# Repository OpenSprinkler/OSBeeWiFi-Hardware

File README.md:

## OpenSprinkler Bee WiFi Eagle Files

This folder contains EagleCAD schematic and board design files for OpenSprinkler Bee WiFi circuit. Please use EagleCAD 7.0 or above to view the files. We generally do not provide BOM, but you can use EagleCAD's BOM script to export a BOM yourself.

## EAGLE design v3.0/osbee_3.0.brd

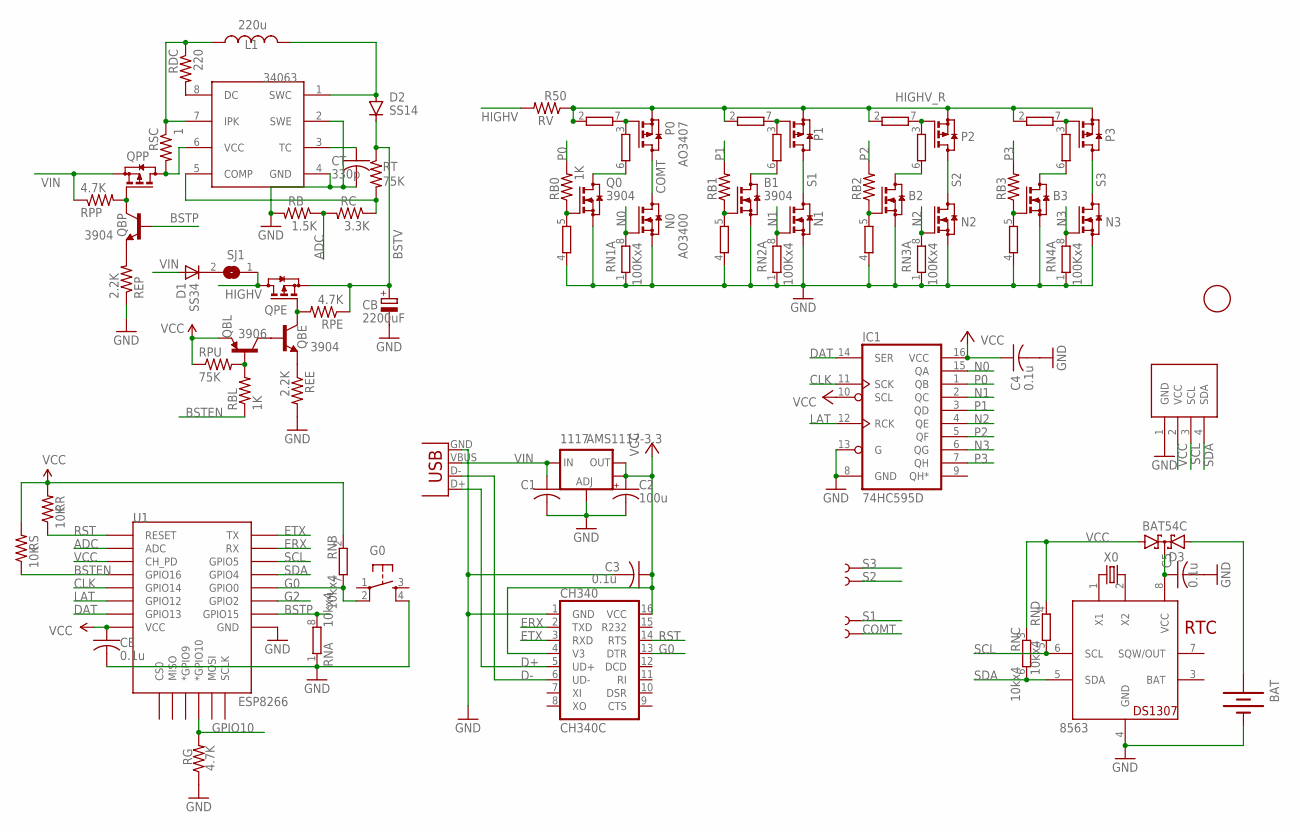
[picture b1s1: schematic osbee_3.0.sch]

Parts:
1F: FIDUCIAL; FIDUCIAL_1MM
1117: AMS1117-3.3; SOT223
8563: PCF8563; SO08
34063: MC34063; SO08
B1, B2, B3: 3904; SOT23
BAT: BATTERYBATTERY_12MM_SMT; BATTCON_12MM_SMT
C1: 10u; C0805K
C2: 100u; PANASONIC_C
C3: 0.1u; C0603K
C4, C5: 0.1u; C0603
CB: 2200uF; E5-8,5
CE: 0.1u; C0603
CH340: CH340C; SO16
CT: 330p; C0603K
D1: SS34; SMB-DIODE
D2: SS14; DO-214AC
D3: BAT54C; SOT23
G0: SPST_TACT; EVQ-Q2-SMD
IC1: 74HC595D; SO16
L1: 220u; CR54
N0, N1, N2, N3: AO3400; SOT23
P0, P1, P2, P3: AO3407; SOT23
Q0: 3904; SOT23
QBE: 3904; SOT23-3
QBL: 3906; SOT23-3
QBP: 3904; SOT23-3
QPE: AO3407; SOT23
QPP: AO3407; SOT23
RB: 1.5K; R0603
RB0, RB1, RB2, RB3: 1K; R0603
RBL: 1K; R0603
RC: 3.3K; R0603
RDC: 220; R0603
REE: 2.2K; R0603
REP: 2.2K; R0603
RG: 4.7K; R0603
RN: 10kx4; EXB38V
RN1, RN2, RN3, RN4: 100Kx4; EXB38V
RPE: 4.7K; R0603
RPP: 4.7K; R0603
RPU: 75K; R0603
RR: 10K; R0603
RS: 10K; R0603
RSC: 1; R0603
RT: 75K; R0603
RV: R50; R2512
SJ1: SJ
ST1, ST2, ST3: NOBOM-; PETAL-9X9
STT: NOBOM-; PETAL-9X9
U1: ESP8266; ESP12E-SMD
U$1: NOBOM-OLED; SSD1306_OLED_I2C_PCB_0.75_BNEW
USB: USBMICROB2; USB-MICROB2
X0: 32.768kHz; 3.2X1.5

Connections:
ADC: RB.1, RC.2, U1.ADC
BAT: 8563.3 (BAT)
BSTEN: RBL.1, RS.1, U1.GPIO16
BSTP: QBP.1 (B), RN.8 (2), U1.GPIO15
BSTV: CB.+, D2.C, QPE.2 (S), RPE.1, RT.1
CLK: IC1.11 (SCK), U1.GPIO14
COMT: N0.3 (D), P0.3 (D), STT.P$1
D+: CH340.5 (UD+), USB.D+
D-: CH340.6 (UD-), USB.D-
DAT: IC1.14 (SER), U1.GPIO13
ERX: CH340.2 (TXD), U1.RXD0 (RX)
ETX: CH340.3 (RXD), U1.TXD0 (TX)
G0: CH340.13 (DTR), G0.2, RN.7 (2), U1.GPIO0
G2: U1.GPIO2
GND: 1117.1 (ADJ), 8563.4 (GND), 34063.2 (SWE), 34063.4 (GND), B1.2 (S), B2.2 (S), B3.2 (S), BAT.P$1 (-), C1.2, C2.-, C3.2, C4.2, C5.2, CB.-, CE.2, CH340.1 (GND), CT.2, G0.4, IC1.8 (GND), IC1.13 (G), N0.2 (S), N1.2 (S), N2.2 (S), N3.2 (S), Q0.2 (S), RB.2, REE.2, REP.1, RG.1, RN.1, RN1.1, RN1.4 (1), RN2.1, RN2.4 (1), RN3.1, RN3.4 (1), RN4.1, RN4.4 (1), U1.GND, U$1.1 (GND), USB.GND
GPIO10: RG.2, U1.GPIO10 (*GPIO10)
HIGHV: QPE.3 (D), RV.2, SJ1.1
HIGHV_R: P0.2 (S), P1.2 (S), P2.2 (S), P3.2 (S), RN1.2 (1), RN2.2 (1), RN3.2 (1), RN4.2 (1), RV.1
LAT: IC1.12 (RCK), U1.GPIO12
N0: IC1.15 (QA), N0.1 (G), RN1.8 (2)
N1: IC1.2 (QC), N1.1 (G), RN2.8 (2)
N2: IC1.4 (QE), N2.1 (G), RN3.8 (2)
N3: IC1.6 (QG), N3.1 (G), RN4.8 (2)
unnamed: P0.1 (G), RN1.3 (1), RN1.7 (2)
unnamed: QBP.3 (C), QPP.1 (G), RPP.2
unnamed: Q0.3 (D), RN1.6 (2)
unnamed: B1.3 (D), RN2.6 (2)
unnamed: Q0.1 (G), RB0.1, RN1.5 (2)
unnamed: B3.1 (G), RB3.1, RN4.5 (2)
unnamed: P1.1 (G), RN2.3 (1), RN2.7 (2)
unnamed: B3.3 (D), RN4.6 (2)
unnamed: 34063.1 (SWC), D2.A, L1.P$2 (2)
unnamed: D1.C, SJ1.2
unnamed: BAT.P$2 (+), D3.2 (A2)
unnamed: P2.1 (G), RN3.3 (1), RN3.7 (2)
unnamed: B2.3 (D), RN3.6 (2)
unnamed: 8563.1 (X1), X0.1
unnamed: QBL.1 (B), RBL.2, RPU.2
unnamed: P3.1 (G), RN4.3 (1), RN4.7 (2)
unnamed: QBE.1 (B), QBL.3 (C)
unnamed: QBE.2 (E), REE.1
unnamed: B1.1 (G), RB1.1, RN2.5 (2)
unnamed: B2.1 (G), RB2.1, RN3.5 (2)
unnamed: 34063.7 (IPK), L1.P$1 (1), RDC.1, RSC.1
unnamed: 34063.6 (VCC), QPP.3 (D), RSC.2
unnamed: 34063.3 (TC), CT.1
unnamed: 34063.5 (COMP), RC.1, RT.2
unnamed: 8563.2 (X2), X0.2
unnamed: 34063.8 (DC), RDC.2
unnamed: QBP.2 (E), REP.2
unnamed: QBE.3 (C), QPE.1 (G), RPE.2
unnamed: 8563.8 (VCC), C5.1, D3.3 (CC)
P0: IC1.1 (QB), RB0.2
P1: IC1.3 (QD), RB1.2
P2: IC1.5 (QF), RB2.2
P3: IC1.7 (QH), RB3.2
RST: CH340.14 (RTS), RR.1, U1.RESET
S1: N1.3 (D), P1.3 (D), ST1.P$1
S2: N2.3 (D), P2.3 (D), ST2.P$1
S3: N3.3 (D), P3.3 (D), ST3.P$1
SCL: 8563.6 (SCL), RN.5 (2), U1.GPIO5, U$1.3 (SCL)
SDA: 8563.5 (SDA), RN.6 (2), U1.GPIO4, U$1.4 (SDA)
VCC: 1117.2 (OUT), 1117.4 (OUT), C2.+, C3.1, C4.1, CE.1, CH340.4 (V3), CH340.16 (VCC), D3.1 (A1), IC1.10 (SCL), IC1.16 (VCC), QBL.2 (E), RN.2 (1), RN.3 (1), RN.4 (1), RPU.1, RR.2, RS.2, U1.CH_PD, U1.VCC, U$1.2 (VCC)
VIN: 1117.3 (IN), C1.1, D1.A, QPP.2 (S), RPP.1, USB.VBUS

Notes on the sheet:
RTC

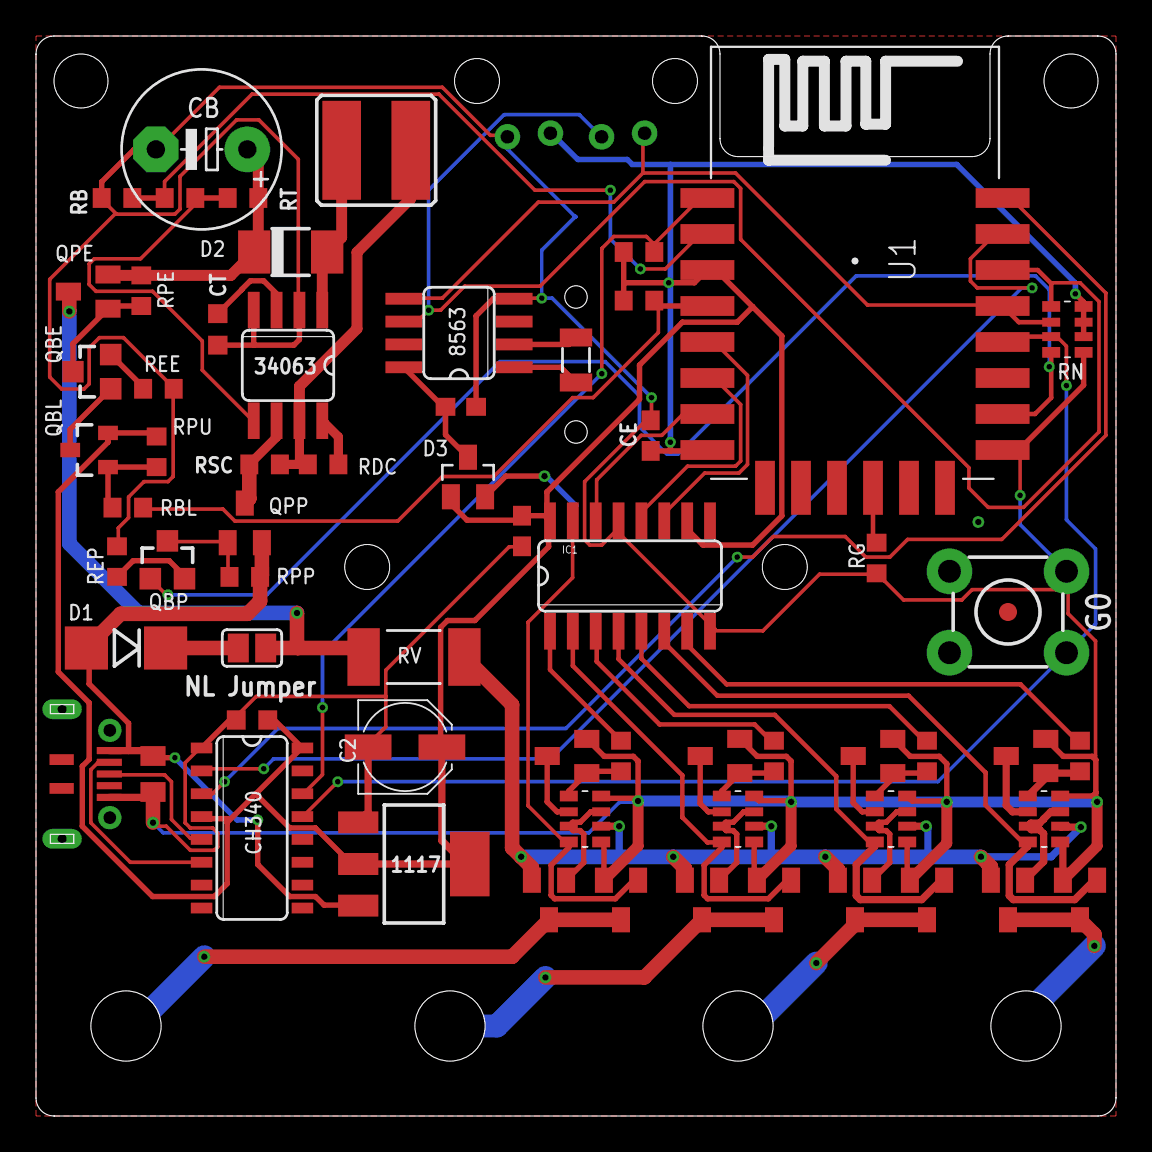
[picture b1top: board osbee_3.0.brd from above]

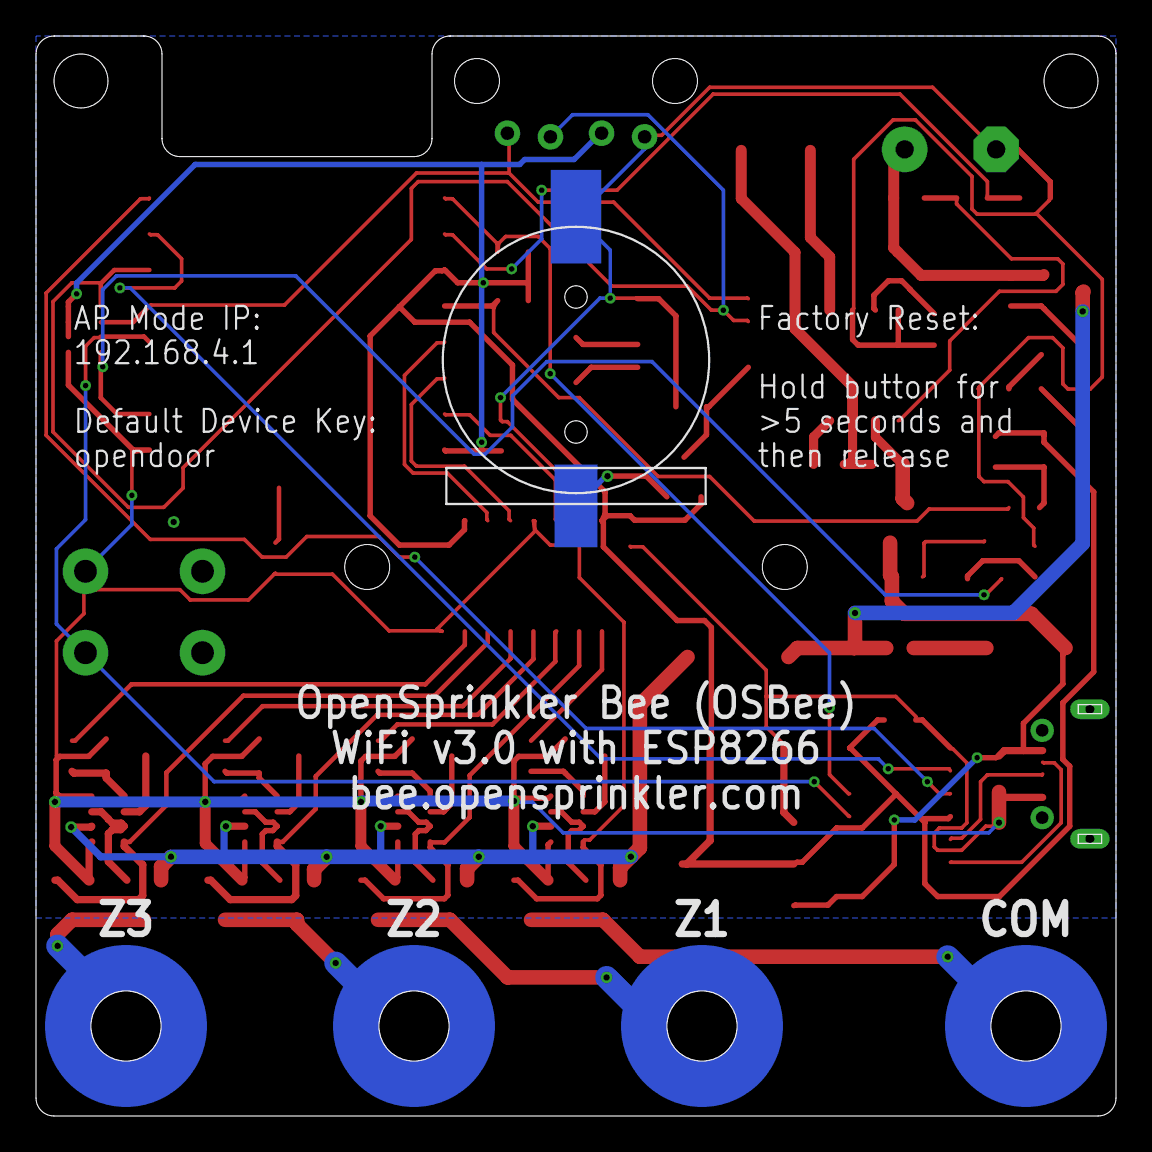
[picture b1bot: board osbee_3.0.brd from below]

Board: 2 copper layers, 60.0 x 60.0 mm, 70 parts (5 on the bottom side), 62 nets.

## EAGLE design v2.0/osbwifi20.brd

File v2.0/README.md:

OpenSprinkler Bee 2.0 Pin Assignments:
===================

- GPIO0:  Button
- GPIO2:  COM 
- GPIO4:  SDA
- GPIO5:  SCL
- GPIO12: Z1
- GPIO13: Z2
- GPIO14: Z3
- GPIO15: BST Power  (High-side Switch 1)
- GPIO16: BST Enable (High-side Switch 2)

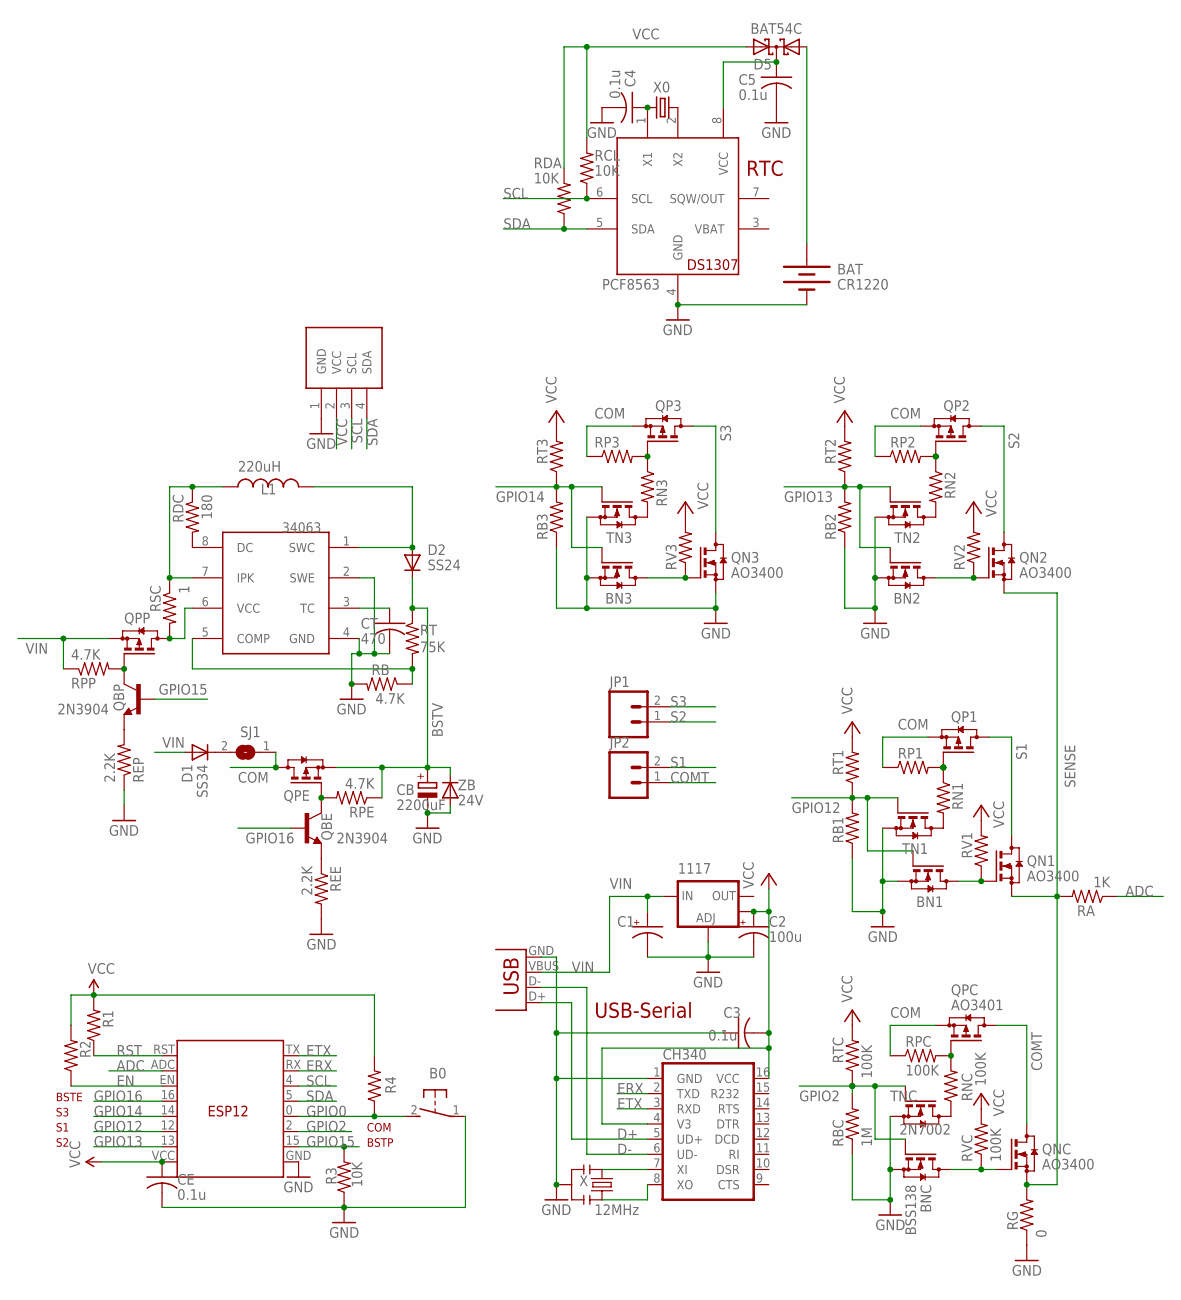
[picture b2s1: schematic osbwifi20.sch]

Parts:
1117: 1117; SOT223
34063: MC33063/MC34063D; SO08
B0: 31-XX; B3F-31XX
BAT: CR1220; BATTCON_12MM_SMT
BN1, BN2, BN3: BSS138; SOT23
BNC: BSS138; SOT23
C1, C2: 100u; B/3528-21R
C3, C4, C5: 0.1u; C0603
CB: 2200uF; E5-8,5
CE: 0.1u; C0603
CH340: CH340G; SO16
CT: 470; C0603K
D1: SS34; SMB
D2: SS24; DO-214AC
D5: BAT54C; SOT23
ESP: ESP; ESP12
JP1, JP2: M025MM; SCREWTERMINAL-5MM-2
L1: 220uH; CR54
PCF8563: PCF8563; SO08
QBE: 2N3904; SOT23-3
QBP: 2N3904; SOT23-3
QN1, QN2, QN3: AO3400; SOT23
QNC: AO3400; SOT23
QP1, QP2, QP3: AO3407; SOT23
QPC: AO3401; SOT23
QPE: AO3401; SOT23
QPP: AO3401; SOT23
R1, R2, R3, R4: 10K; R0603
RA: 1K; R0603
RB: 4.7K; R0603
RB1, RB2, RB3: 1M; R0603
RBC: 1M; R0603
RCL: 10K; R0603
RDA: 10K; R0603
RDC: 180; R0603
REE: 2.2K; R0603
REP: 2.2K; R0603
RG: 0; R2512
RN1, RN2, RN3: 100K; R0603
RNC: 100K; R0603
RP1, RP2, RP3: 100K; R0603
RPC: 100K; R0603
RPE: 4.7K; R0603
RPP: 4.7K; R0603
RSC: 1; R0603
RT: 75K; R0603
RT1, RT2, RT3: 100K; R0603
RTC: 100K; R0603
RV1, RV2, RV3: 100K; R0603
RVC: 100K; R0603
SJ1: SJ
TN1, TN2, TN3: 7002; SOT23
TNC: 2N7002; SOT23
U$1: SSD1306_OLED_I2C
USB: USBSMD; USB-MINIB
X: 12MHz; RESONATOR-SMD
X0: 32.768kHz; MM20SS1
ZB: 24V; MINIMELF

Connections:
ADC: ESP.ADC, RA.1
BSTV: CB.+, D2.C, QPE.2 (S), RPE.1, RT.1, ZB.C
COM: QP1.2 (S), QP2.2 (S), QP3.2 (S), QPC.2 (S), QPE.3 (D), RP1.1, RP2.1, RP3.1, RPC.1, SJ1.1
COMT: JP2.1, QNC.3 (D), QPC.3 (D)
D+: CH340.5 (UD+), USB.D+
D-: CH340.6 (UD-), USB.D-
EN: ESP.EN, R2.1
ERX: CH340.2 (TXD), ESP.RX
ETX: CH340.3 (RXD), ESP.TX
GND: 1117.1 (ADJ), 34063.2 (SWE), 34063.4 (GND), B0.1, BAT.P$1 (-), BN1.2 (S), BN2.2 (S), BN3.2 (S), BNC.2 (S), C1.-, C2.-, C3.1, C4.2, C5.2, CB.-, CE.2, CH340.1 (GND), CT.2, ESP.GND, PCF8563.4 (GND), QN3.2 (S), R3.1, RB.2, RB1.1, RB2.1, RB3.1, RBC.1, REE.2, REP.1, RG.1, TN1.2 (S), TN2.2 (S), TN3.2 (S), TNC.2 (S), U$1.1 (GND), USB.GND, X.2, ZB.A
GPIO0: B0.2 (S), ESP.0 (G0), R4.1
GPIO2: BNC.1 (G), ESP.2 (G2), RBC.2, RTC.1, TNC.1 (G)
GPIO12: BN1.1 (G), ESP.12 (G12), RB1.2, RT1.1, TN1.1 (G)
GPIO13: BN2.1 (G), ESP.13 (G13), RB2.2, RT2.1, TN2.1 (G)
GPIO14: BN3.1 (G), ESP.14 (G14), RB3.2, RT3.1, TN3.1 (G)
GPIO15: ESP.15 (G15), QBP.1 (B), R3.2
GPIO16: ESP.16 (G16), QBE.1 (B)
unnamed: QPC.1 (G), RNC.2, RPC.2
unnamed: QBP.3 (C), QPP.1 (G), RPP.2
unnamed: RNC.1, TNC.3 (D)
unnamed: RN1.2, TN1.3 (D)
unnamed: BNC.3 (D), QNC.1 (G), RVC.1
unnamed: CH340.7 (XI), X.1
unnamed: QP1.1 (G), RN1.1, RP1.2
unnamed: RN3.2, TN3.3 (D)
unnamed: 34063.1 (SWC), D2.A, L1.P$2 (2)
unnamed: D1.C, SJ1.2
unnamed: BN1.3 (D), QN1.1 (G), RV1.1
unnamed: QP2.1 (G), RN2.1, RP2.2
unnamed: RN2.2, TN2.3 (D)
unnamed: C4.1, PCF8563.1 (X1), X0.1
unnamed: BN2.3 (D), QN2.1 (G), RV2.1
unnamed: QP3.1 (G), RN3.1, RP3.2
unnamed: BAT.P$2 (+), D5.1 (A1)
unnamed: BN3.3 (D), QN3.1 (G), RV3.1
unnamed: QBE.2 (E), REE.1
unnamed: 34063.7 (IPK), L1.P$1 (1), RDC.1, RSC.1
unnamed: 34063.6 (VCC), QPP.3 (D), RSC.2
unnamed: 34063.3 (TC), CT.1
unnamed: 34063.5 (COMP), RB.1, RT.2
unnamed: PCF8563.2 (X2), X0.4 (2)
unnamed: 34063.8 (DC), RDC.2
unnamed: QBP.2 (E), REP.2
unnamed: QBE.3 (C), QPE.1 (G), RPE.2
unnamed: CH340.8 (XO), X.3
unnamed: C5.1, D5.3 (CC), PCF8563.8 (VCC)
RST: ESP.RST, R1.1
S1: JP2.2, QN1.3 (D), QP1.3 (D)
S2: JP1.1, QN2.3 (D), QP2.3 (D)
S3: JP1.2, QN3.3 (D), QP3.3 (D)
SCL: ESP.4 (G4), PCF8563.6 (SCL), RCL.1, U$1.3 (SCL)
SDA: ESP.5 (G5), PCF8563.5 (SDA), RDA.1, U$1.4 (SDA)
SENSE: QN1.2 (S), QN2.2 (S), QNC.2 (S), RA.2, RG.2
VBAT: PCF8563.3 (VBAT)
VCC: 1117.4 (OUT), C2.+, C3.2, CE.1, CH340.4 (V3), CH340.16 (VCC), D5.2 (A2), ESP.VCC, R1.2, R2.2, R4.2, RCL.2, RDA.2, RT1.2, RT2.2, RT3.2, RTC.2, RV1.2, RV2.2, RV3.2, RVC.2, U$1.2 (VCC)
VIN: 1117.3 (IN), C1.+, D1.A, QPP.2 (S), RPP.1, USB.VBUS

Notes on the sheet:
USB-Serial
BSTP
BSTE
RTC
COM

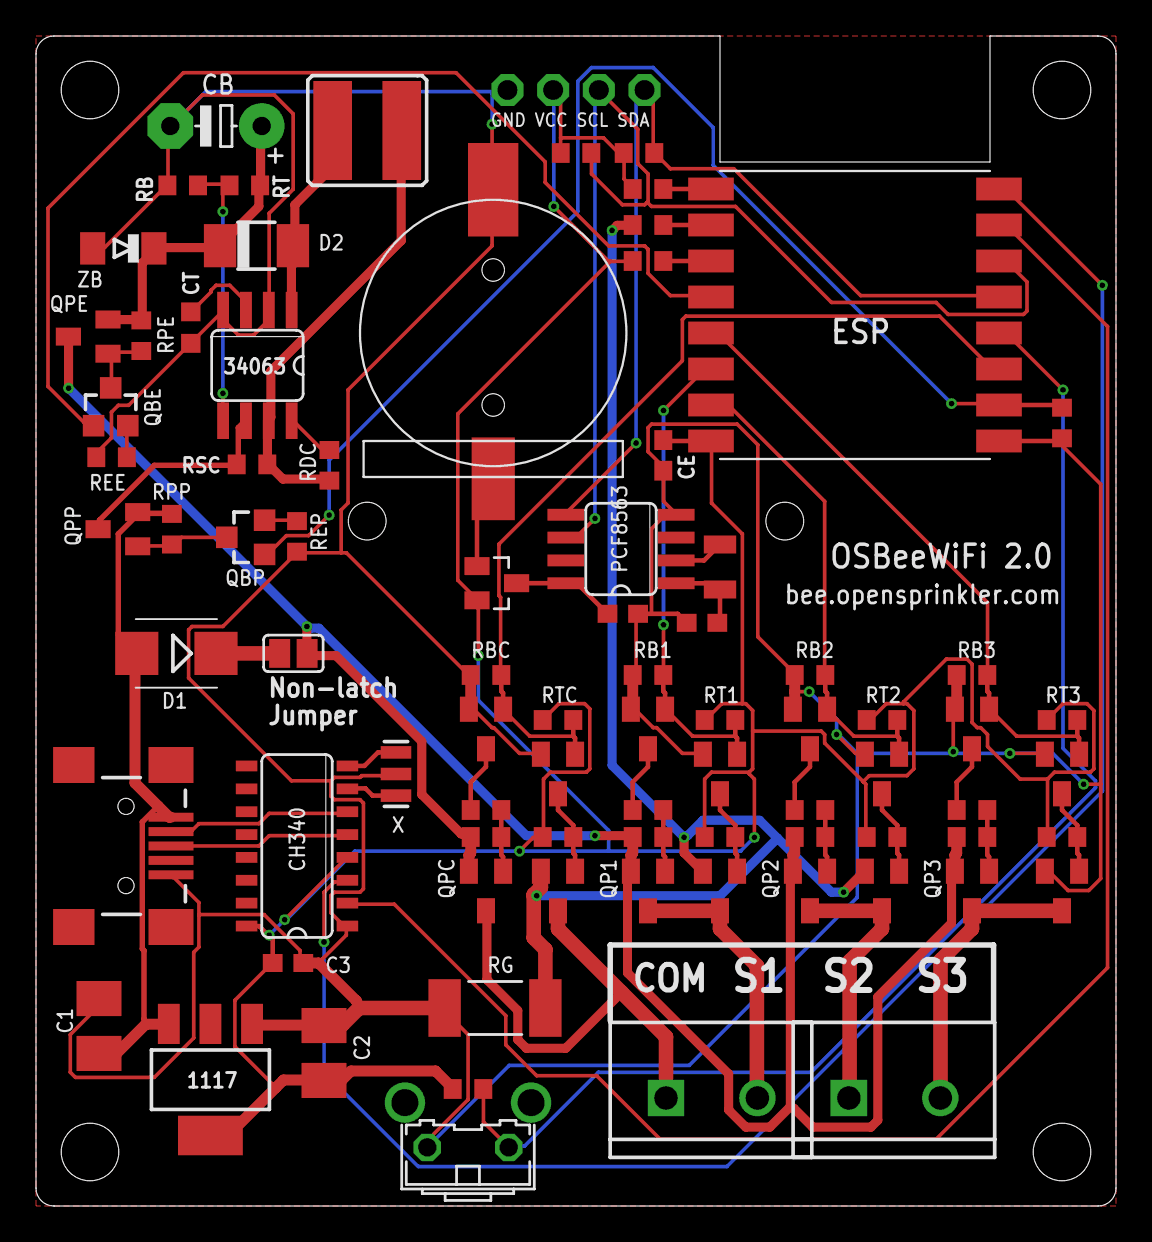
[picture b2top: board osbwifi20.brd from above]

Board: 2 copper layers, 60.0 x 65.0 mm, 83 parts (0 on the bottom side), 55 nets.

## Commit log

2016-12-05 check in initial version of OSBeeWiFi Eagle files
2016-12-05 add README
2016-12-11 add pin assignments
2021-09-07 add v3.0 hardware design files
2023-06-05 add enclosure 3d print file for osbee3

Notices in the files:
parts and their libraries:
crystal-geyer_V1_0: Copyright: Geyer-Electronic
